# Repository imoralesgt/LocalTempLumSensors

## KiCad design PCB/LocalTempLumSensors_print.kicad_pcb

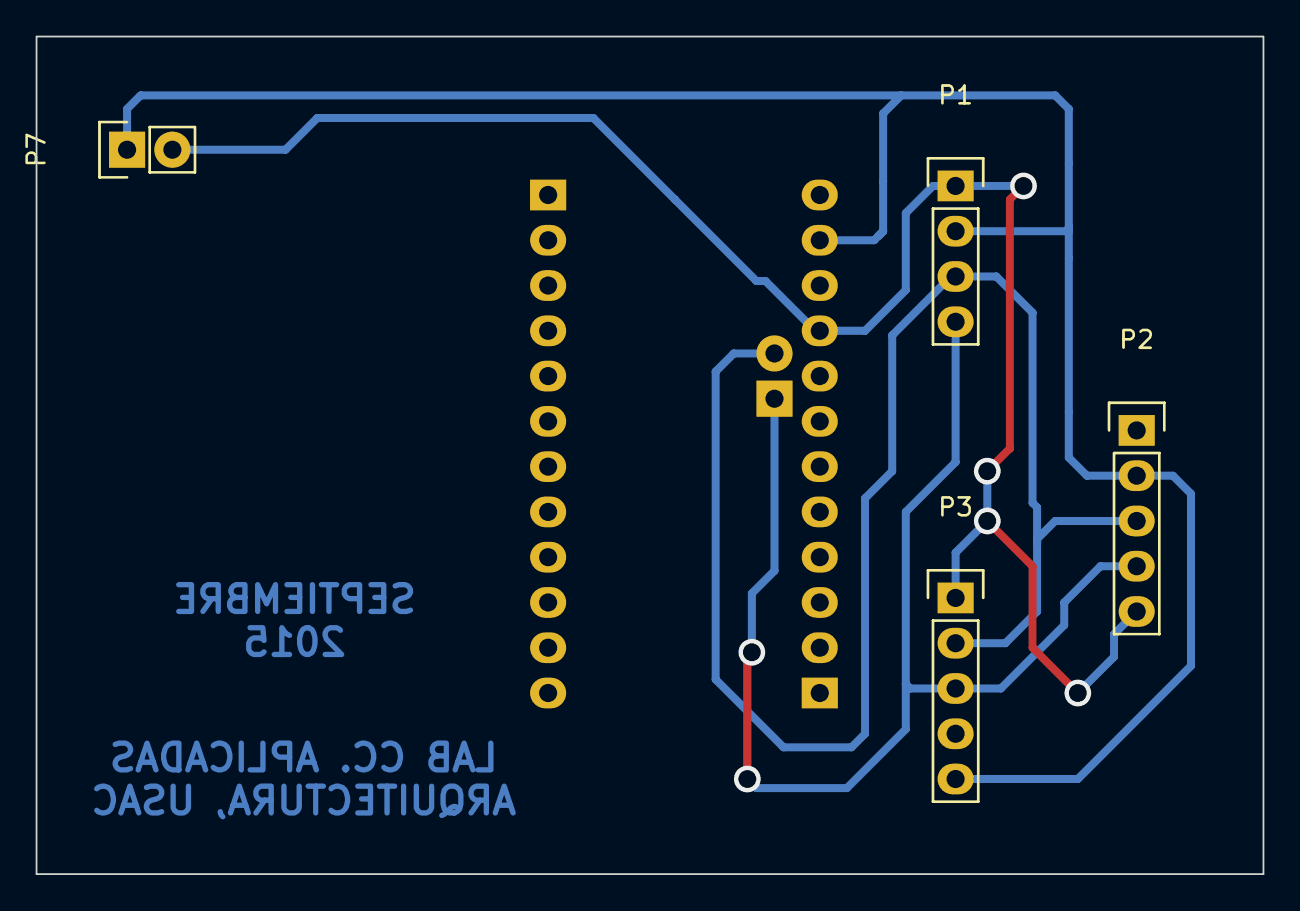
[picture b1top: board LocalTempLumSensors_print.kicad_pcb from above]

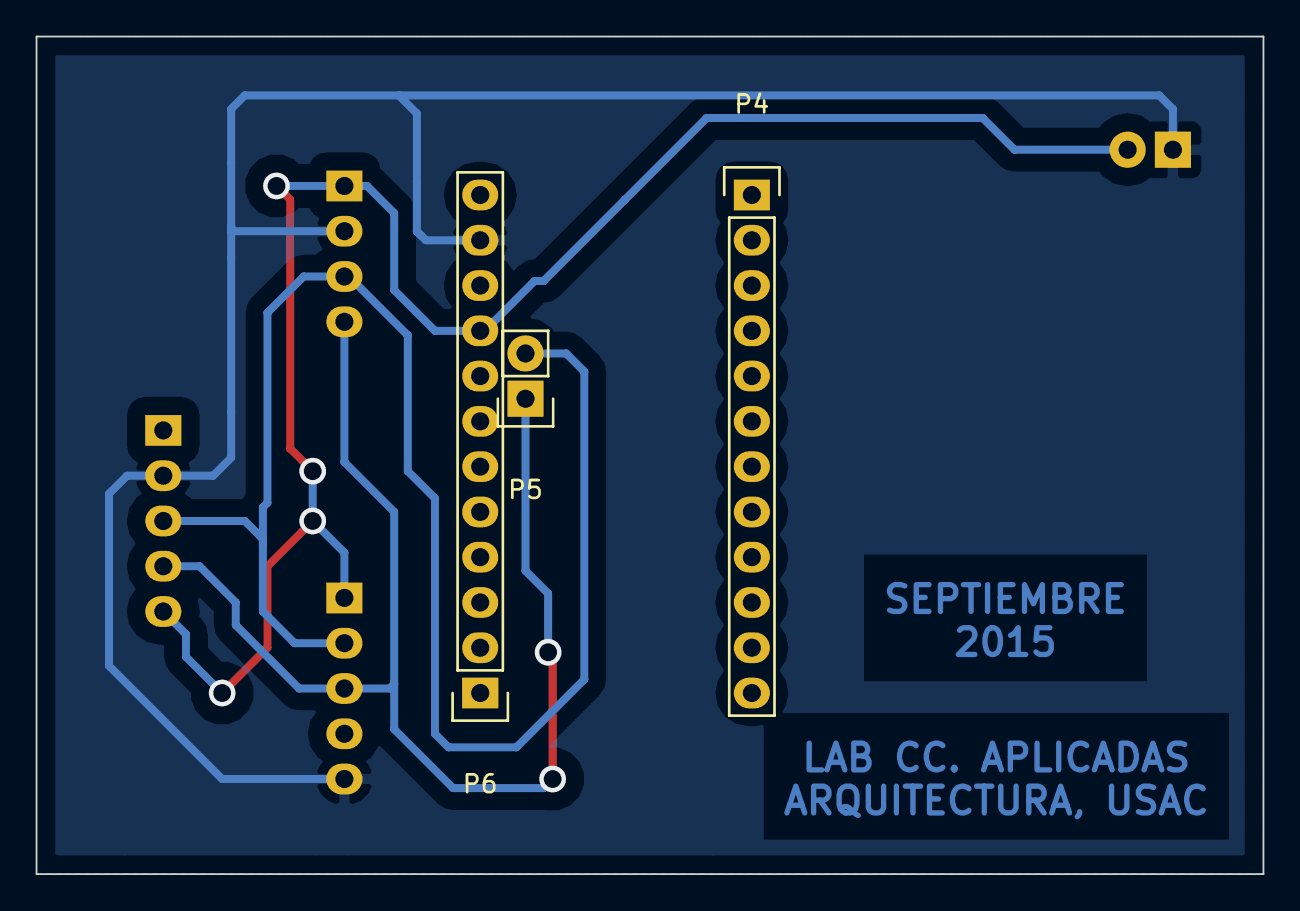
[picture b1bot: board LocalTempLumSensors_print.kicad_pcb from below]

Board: 2 copper layers, 68.8 x 47.0 mm, 7 parts (3 on the bottom side), 4 nets.

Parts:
P1: OLED DISPLAY; Pin_Header_Straight_1x04
P2: BMP 180; Pin_Header_Straight_1x05
P3: BH1750; Pin_Header_Straight_1x05
P4: ARDUINO_LEFT; Pin_Header_Straight_1x12
P5: ARDUINO_I2C; Pin_Header_Straight_1x02
P6: ARDUINO_RIGHT; Pin_Header_Straight_1x12
P7: POWER; Pin_Header_Straight_1x02

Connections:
/SCL: P1.3, P2.3, P3.2, P5.2
/SDA: P1.4, P2.4, P3.3, P5.1
GND: P1.2, P2.2, P3.5, P6.11, P7.1
VCC: P1.1, P2.5, P3.1, P6.9, P7.2

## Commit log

2015-08-13 :boom::camel: Added .gitattributes & .gitignore files
2015-08-13 Set of libraries to be used
2015-08-21 Splash screen test on OLED display
2015-08-21 Fixed "SENSOR" position
2015-08-24 Initial commit with sensors display on OLED
2015-08-25 First schematic and footprint commit
    Schematic in KiCAD
    Footprint in AutoCAD
2015-09-09 PCB preliminary design done
2015-09-17 New PCB design - fixed misplaced BH1750
2015-09-17 Fixed I2C inverted pins
    Also fixed OLED display and battery connector positions. Seems to be
    everything nice now, though!
